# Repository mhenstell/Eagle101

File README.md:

Eagle101
========

Slides and supporting documents for the Eagle 101 class taught by Max Henstell at NYC Resistor.

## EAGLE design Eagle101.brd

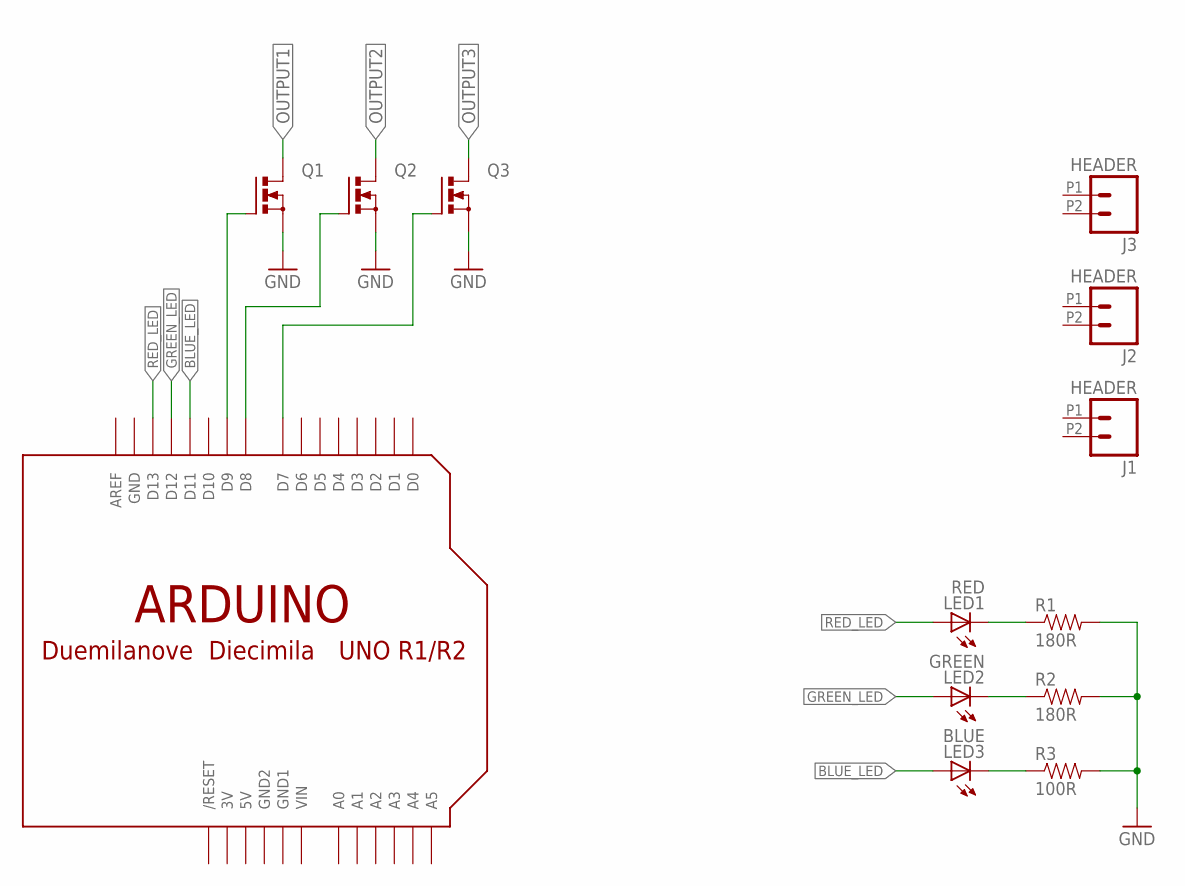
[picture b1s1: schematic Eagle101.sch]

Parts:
J1, J2, J3: HEADER; 0.2-SCREWTERM
LED1: RED; LED5MM
LED2: GREEN; LED5MM
LED3: BLUE; LED5MM
Q1, Q2, Q3: PMOSFET_NTO220BH; TO220BH
R1, R2: 180R; AXIAL-0.4
R3: 100R; AXIAL-0.4
U$1: ARDUINO-BPLACE

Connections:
3V: U$1.3V
5V: U$1.5V
BLUE_LED: LED3.A, U$1.D11
GND: Q1.S, Q2.S, Q3.S, R1.P$2 (2), R2.P$2 (2), R3.P$2 (2), U$1.GND
GND1: U$1.GND1
GND2: U$1.GND2
GREEN_LED: LED2.A, U$1.D12
unnamed: Q1.G, U$1.D9
unnamed: Q2.G, U$1.D8
unnamed: Q3.G, U$1.D7
unnamed: LED1.K (C), R1.P$1 (1)
unnamed: LED2.K (C), R2.P$1 (1)
unnamed: LED3.K (C), R3.P$1 (1)
OUTPUT1: Q1.D
OUTPUT2: Q2.D
OUTPUT3: Q3.D
RED_LED: LED1.A, U$1.D13
VIN: U$1.VIN

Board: 2 copper layers, 13 parts (0 on the bottom side), 10 nets, no tracks yet.

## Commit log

2014-07-13 init
2014-07-14 unfinished schematic, libraries

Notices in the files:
parts and their libraries:
SparkFun-Passives: Licensing: Creative Commons ShareAlike 4.0 International - https://creativecommons.org/licenses/by-sa/4.0
